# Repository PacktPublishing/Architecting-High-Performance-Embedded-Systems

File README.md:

# Architecting High-Performance Embedded Systems

This is the code repository for [Architecting High-Performance Embedded Systems](https://www.packtpub.com/product/architecting-high-performance-embedded-systems/9781789955965?utm_source=github&utm_medium=repository&utm_campaign=9781789955965), published by Packt.

**Design and build high-performance real-time digital systems based on FPGAs and custom circuits**

## What is this book about?
Modern digital devices used in homes, cars, and wearables contain highly sophisticated computing capabilities composed of embedded systems that generate, receive, and process digital data streams at rates up to multiple gigabits per second. This book will show you how to use Field Programmable Gate Arrays (FPGAs) and high-speed digital circuit design to create your own cutting-edge digital systems. 

This book covers the following exciting features:
* Understand the fundamentals of real-time embedded systems and sensors
* Discover the capabilities of FPGAs and how to use FPGA development tools
* Learn the principles of digital circuit design and PCB layout with KiCad
* Construct high-speed circuit board prototypes at low cost
* Design and develop high-performance algorithms for FPGAs
Develop robust, reliable, and efficient firmware in C
Thoroughly test and debug embedded device hardware and firmware

If you feel this book is for you, get your [copy](https://www.amazon.com/dp/1789955963) today!

## Instructions and Navigation
All of the code is organized into folders based on chapter number.

**What you need to work with the examples in this book:**
This book is for software developers, IoT engineers, and anyone who wants to understand the process of developing high-performance embedded systems. You’ll also find this book useful if you want to learn about the fundamentals of FPGA development and all aspects of firmware development in C and C++. Familiarity with the C language, digital circuits, and electronic soldering is necessary to get started.

With the following software and hardware you can run all code files present in the book.
### Software and Hardware List
| Software or hardware | OS required |
| ------------------------------------ | ----------------------------------- |
| [Xilinx Vivado](https://www.xilinx.com/support/download.html) | Windows, Mac OS X, and Linux (Any) |
| [KiCad](https://kicad.org/download/) | Windows, Mac OS X, and Linux (Any) |
| [Arty A7-100](https://www.xilinx.com/products/boards-and-kits/1-w51quh.html) | Windows, Mac OS X, and Linux (Any) |

We also provide a PDF file that has color images of the screenshots/diagrams used in this book. [Click here to download it](https://static.packt-cdn.com/downloads/9781789955965_ColorImages.pdf).

## Get to Know the Author
**Jim Ledin**
Jim Ledin is the CEO of Ledin Engineering, Inc. Jim is an expert in embedded software and hardware design, development, and testing. He is also accomplished in embedded system cybersecurity assessment and penetration testing. He has a B.S. degree in aerospace engineering from Iowa State University and an M.S. degree in electrical and computer engineering from Georgia Institute of Technology. Jim is a registered professional electrical engineer in California, a Certified Information System Security Professional (CISSP), a Certified Ethical Hacker (CEH), and a Certified Penetration Tester (CPT).

## Other books by the author
* Modern Computer Architecture and Organization [[Packt]](https://www.packtpub.com/in/cloud-networking/modern-computer-architecture-and-organization?utm_source=github&utm_medium=repository&utm_campaign=9781838984397) [[Amazon]](https://www.amazon.com/dp/1838984399)
### Download a free PDF

 <i>If you have already purchased a print or Kindle version of this book, you can get a DRM-free PDF version at no cost.<br>Simply click on the link to claim your free PDF.</i>
<p align="center"> <a href="https://packt.link/free-ebook/9781789955965">https://packt.link/free-ebook/9781789955965 </a> </p>

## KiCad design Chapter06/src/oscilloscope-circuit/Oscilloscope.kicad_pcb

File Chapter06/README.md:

__Architecting-High-Performance-Embedded-Systems__, by Jim Ledin. Published by Packt Publishing.
# Chapter 6 - Designing circuits with KiCad

This chapter introduces the excellent open source KiCad electronics design and automation suite. Working in KiCad, you design a circuit with schematic diagrams and develop a corresponding printed circuit board layout. You’ll learn how to turn a circuit board design into a prototype at a very reasonable cost. The chapter includes example schematics from the oscilloscope circuit project you will assemble in the next chapter.

After completing this chapter, you will have downloaded and installed KiCad, learned how to create circuit schematics in KiCad, learned to develop circuit board layouts in KiCad, and you will have worked through portions of the circuit board design for the digital oscilloscope project.

We will cover the following topics in this chapter: 
* Introducing KiCad
* Basic KiCad procedures
* Developing the project schematic diagram
* Laying out the PCB
* Prototyping the circuit board

# Chapter Files

[oscilloscope-circuit project](src/oscilloscope-circuit) contains the KiCad schematic diagram and PCB layout project for the digital oscilloscope circuit design we worked through in Chapter 6.

__Notes:__
* Before opening the schematic diagram, open the KiCad project manager and add *Schematic Symbols.lib* as a library using *Preferences/Manage Symbol Libraries...*
* Before opening the PCB layout, open the KiCad project manager and add the directory *Footprints.pretty* as a library using *Preferences/Manage Footprint Libraries...*

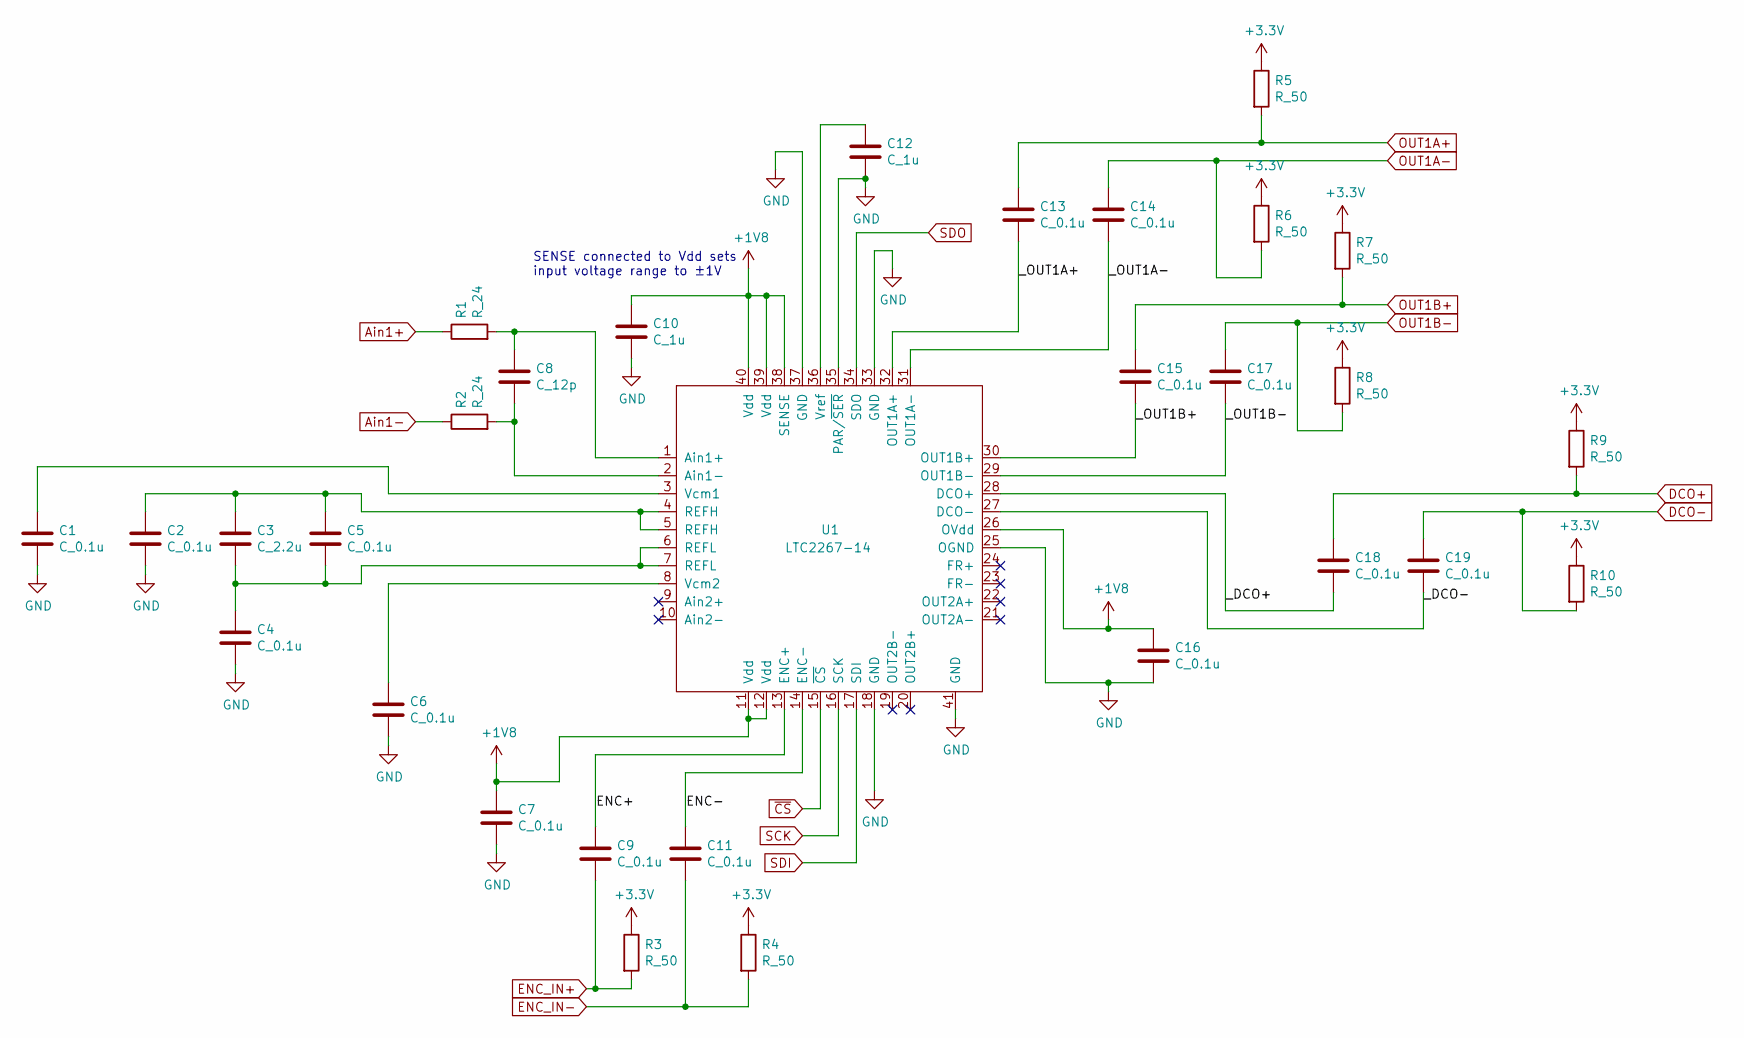
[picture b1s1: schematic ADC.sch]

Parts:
C1, C2, C4, C5, C6, C7, C9, C11, C13, C14, C15, C16, C17, C18, C19: C_0.1u; C_0402_1005Metric
C3: C_2.2u; C_0603_1608Metric
C8: C_12p; C_0402_1005Metric
C10, C12: C_1u; C_0603_1608Metric
R1, R2: R_24; R_0402_1005Metric
R3, R4, R5, R6, R7, R8, R9, R10: R_50; R_0402_1005Metric
U1: LTC2267-14; QFN-40-1EP_6x6mm_P0.5mm_EP4.6x4.6mm_ThermalVias

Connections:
+1V8: C7.1, C10.1, C16.1, U1.11 (Vdd), U1.12 (Vdd), U1.26 (OVdd), U1.38 (SENSE), U1.39 (Vdd), U1.40 (Vdd); also elsewhere on the board
+3V3: R3.1, R4.1, R5.1, R6.1, R7.1, R8.1, R9.1, R10.1; also elsewhere on the board
/ADC/ENC+: C9.1, U1.13 (ENC+)
/ADC/ENC-: C11.1, U1.14 (ENC-)
/ADC/_DCO+: C18.2, U1.28 (DCO+)
/ADC/_DCO-: C19.2, U1.27 (DCO-)
/ADC/_OUT1A+: C13.2, U1.32 (OUT1A+)
/ADC/_OUT1A-: C14.2, U1.31 (OUT1A-)
/ADC/_OUT1B+: C15.2, U1.30 (OUT1B+)
/ADC/_OUT1B-: C17.2, U1.29 (OUT1B-)
Ain1+: R1.1; also elsewhere on the board
Ain1-: R2.1; also elsewhere on the board
DCO+: C18.1, R9.2; also elsewhere on the board
DCO-: C19.1, R10.2; also elsewhere on the board
ENC_IN+: C9.2, R3.2; also elsewhere on the board
ENC_IN-: C11.2, R4.2; also elsewhere on the board
GND: C1.2, C2.2, C4.2, C6.2, C7.2, C10.2, C12.2, C16.2, U1.18 (GND), U1.25 (OGND), U1.33 (GND), U1.35 (PAR/~SER), U1.37 (GND), U1.41 (GND); also elsewhere on the board
unnamed: C1.1, U1.3 (Vcm1)
unnamed: C2.1, C3.1, C5.1, U1.4 (REFH), U1.5 (REFH)
unnamed: C3.2, C4.1, C5.2, U1.6 (REFL), U1.7 (REFL)
unnamed: C6.1, U1.8 (Vcm2)
unnamed: C8.1, R1.2, U1.1 (Ain1+)
unnamed: C8.2, R2.2, U1.2 (Ain1-)
unnamed: C12.1, U1.36 (Vref)
OUT1A+: C13.1, R5.2; also elsewhere on the board
OUT1A-: C14.1, R6.2; also elsewhere on the board
OUT1B+: C15.1, R7.2; also elsewhere on the board
OUT1B-: C17.1, R8.2; also elsewhere on the board
SCK: U1.16 (SCK); also elsewhere on the board
SDI: U1.17 (SDI); also elsewhere on the board
SDO: U1.34 (SDO); also elsewhere on the board
~CS: U1.15 (~CS); also elsewhere on the board

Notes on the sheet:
SENSE connected to Vdd sets input voltage range to ±1V

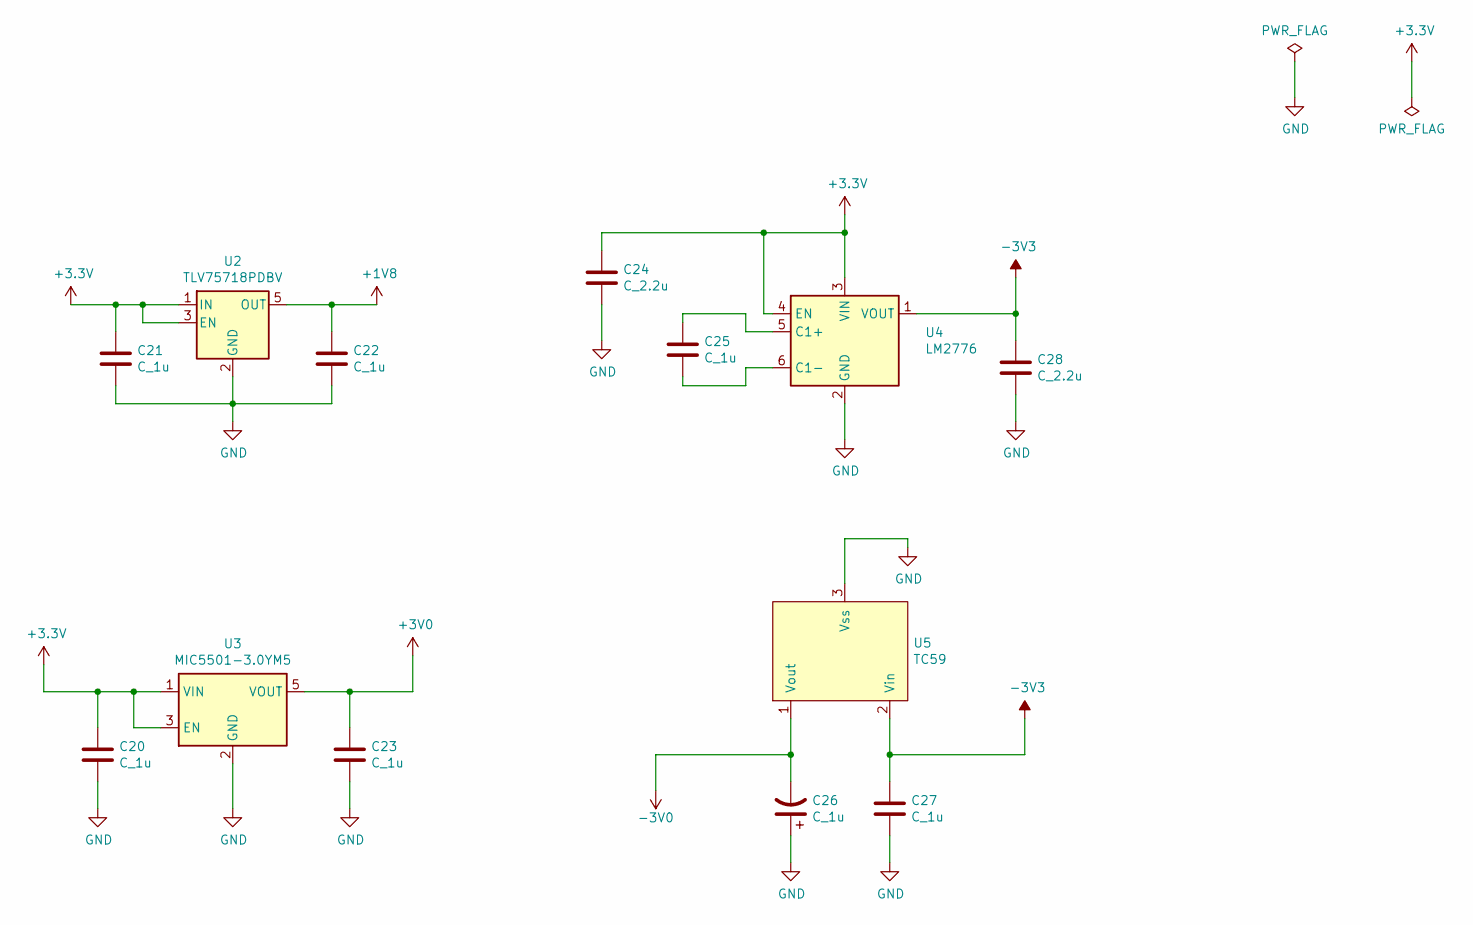
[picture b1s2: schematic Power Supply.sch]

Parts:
C20, C21, C22, C23, C25, C27: C_1u; C_0603_1608Metric
C24, C28: C_2.2u; C_0603_1608Metric
C26: C_1u; CP_EIA-2012-12_Kemet-R
U2: TLV75718PDBV; SOT-23-5
U3: MIC5501-3.0YM5; SOT-23-5
U4: LM2776; SOT-23-6
U5: TC59; SOT-23

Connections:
+1V8: C22.1, U2.5 (OUT); also elsewhere on the board
+3V0: C23.1, U3.5 (VOUT); also elsewhere on the board
+3V3: C20.1, C21.1, C24.1, U2.1 (IN), U2.3 (EN), U3.1 (VIN), U3.3 (EN), U4.3 (VIN), U4.4 (EN); also elsewhere on the board
-3V0: C26.2, U5.1 (Vout); also elsewhere on the board
-3V3: C27.1, C28.1, U4.1 (VOUT), U5.2 (Vin)
GND: C20.2, C21.2, C22.2, C23.2, C24.2, C26.1, C27.2, C28.2, U2.2 (GND), U3.2 (GND), U4.2 (GND), U5.3 (Vss); also elsewhere on the board
unnamed: C25.1, U4.5 (C1+)
unnamed: C25.2, U4.6 (C1-)

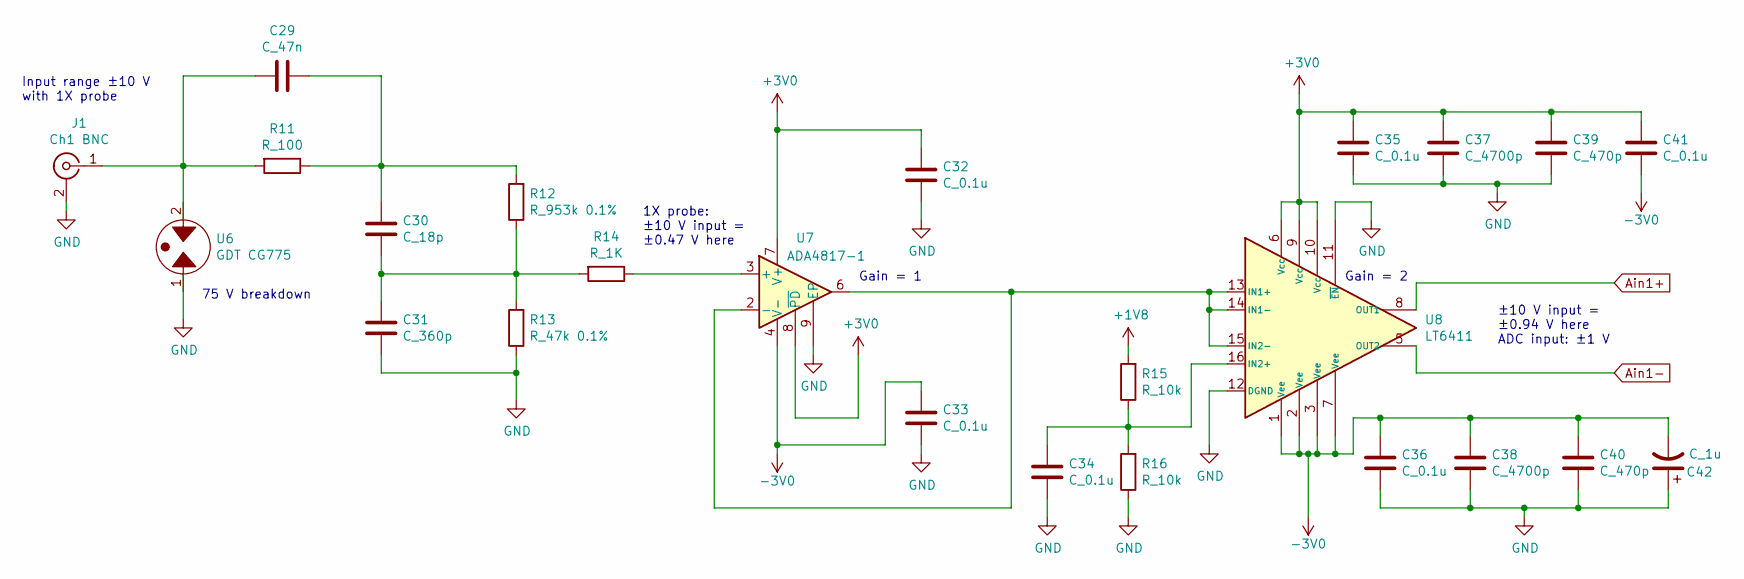
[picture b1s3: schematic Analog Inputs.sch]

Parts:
C29: C_47n; C_0402_1005Metric
C30: C_18p; C_0402_1005Metric
C31: C_360p; C_0402_1005Metric
C32, C33, C34, C35, C36, C41: C_0.1u; C_0402_1005Metric
C37, C38: C_4700p; C_0402_1005Metric
C39, C40: C_470p; C_0402_1005Metric
C42: C_1u; CP_EIA-2012-12_Kemet-R
J1: Ch1 BNC; BNC_Amphenol_B6252HB-NPP3G-50_Horizontal
R11: R_100; R_0402_1005Metric
R12: R_953k 0.1%; R_0402_1005Metric
R13: R_47k 0.1%; R_0402_1005Metric
R14: R_1K; R_0402_1005Metric
R15, R16: R_10k; R_0402_1005Metric
U6: GDT CG775; Littelfuse-GTCC23-XXXM-R01-2-Series-GDT
U7: ADA4817-1; SOIC-8-1EP_3.9x4.9mm_P1.27mm_EP2.29x3mm
U8: LT6411; QFN-16-1EP_3x3mm_P0.5mm_EP1.7x1.7mm

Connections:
+1V8: R15.2; also elsewhere on the board
+3V0: C32.2, C35.2, C37.2, C39.2, C41.2, U7.7 (V+), U7.8 (~PD), U8.6 (Vcc), U8.9 (Vcc), U8.10 (Vcc); also elsewhere on the board
-3V0: C33.2, C36.2, C38.2, C40.2, C41.1, C42.2, U7.4 (V-), U8.1 (Vee), U8.2 (Vee), U8.3 (Vee), U8.7 (Vee); also elsewhere on the board
Ain1+: U8.8 (OUT1); also elsewhere on the board
Ain1-: U8.5 (OUT2); also elsewhere on the board
GND: C31.1, C32.1, C33.1, C34.1, C35.1, C36.1, C37.1, C38.1, C39.1, C40.1, C42.1, J1.2 (Ext), R13.1, R16.1, U6.1, U7.9 (EP), U8.11 (~EN), U8.12 (DGND); also elsewhere on the board
unnamed: C29.1, C30.2, R11.1, R12.2
unnamed: C29.2, J1.1 (In), R11.2, U6.2
unnamed: C30.1, C31.2, R12.1, R13.2, R14.2
unnamed: C34.2, R15.1, R16.2, U8.16 (IN2+)
unnamed: R14.1, U7.3 (+)
unnamed: U7.2 (-), U7.6, U8.13 (IN1+), U8.14 (IN1-), U8.15 (IN2-)

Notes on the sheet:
Input range ±10 V with 1X probe
Gain = 2
1X probe: ±10 V input = ±0.47 V here
±10 V input = ±0.94 V here ADC input: ±1 V
Gain = 1
75 V breakdown

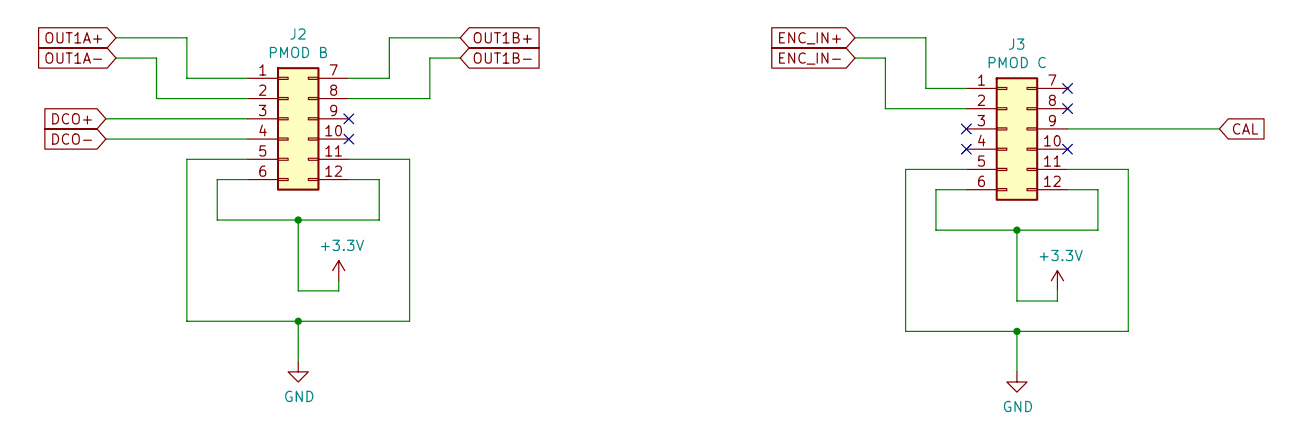
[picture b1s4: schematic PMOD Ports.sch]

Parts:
J2: PMOD B; PinHeader_2x06_P2.54mm_renumbered
J3: PMOD C; PinHeader_2x06_P2.54mm_renumbered

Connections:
+3V3: J2.6, J2.12, J3.6, J3.12; also elsewhere on the board
CAL: J3.9; also elsewhere on the board
DCO+: J2.3; also elsewhere on the board
DCO-: J2.4; also elsewhere on the board
ENC_IN+: J3.1; also elsewhere on the board
ENC_IN-: J3.2; also elsewhere on the board
GND: J2.5, J2.11, J3.5, J3.11; also elsewhere on the board
OUT1A+: J2.1; also elsewhere on the board
OUT1A-: J2.2; also elsewhere on the board
OUT1B+: J2.7; also elsewhere on the board
OUT1B-: J2.8; also elsewhere on the board

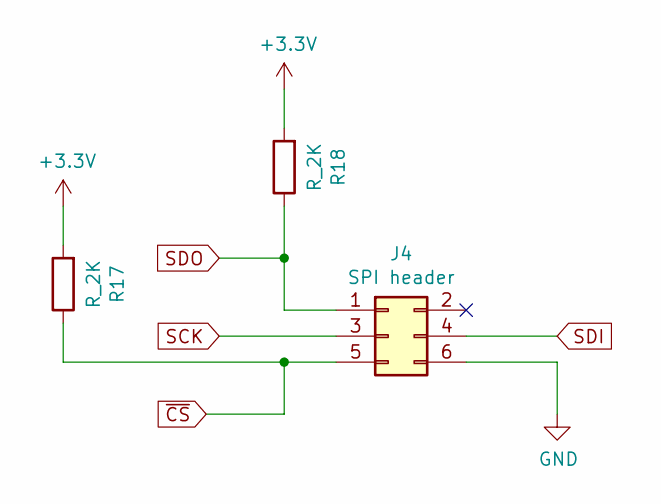
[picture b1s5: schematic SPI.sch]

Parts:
J4: SPI header; PinHeader_2x03_P2.54mm_Vertical
R17, R18: R_2K; R_0402_1005Metric

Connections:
+3V3: R17.2, R18.2; also elsewhere on the board
GND: J4.6; also elsewhere on the board
SCK: J4.3; also elsewhere on the board
SDI: J4.4; also elsewhere on the board
SDO: J4.1, R18.1; also elsewhere on the board
~CS: J4.5, R17.1; also elsewhere on the board

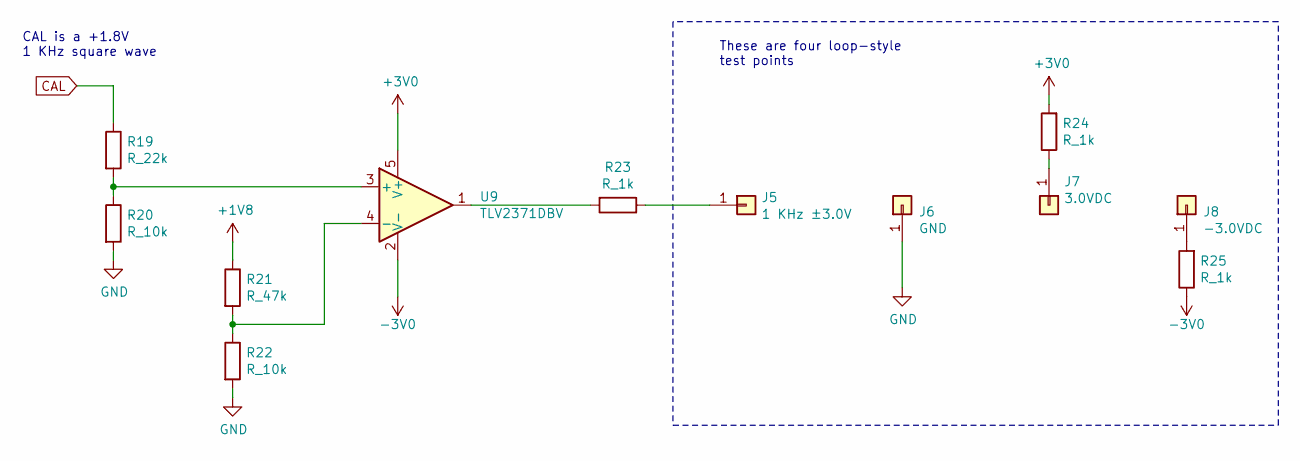
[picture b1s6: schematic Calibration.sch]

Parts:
J5: 1 KHz ±3.0V; TestPoint_Loop_D2.60mm_Drill1.6mm_Beaded
J6: GND; TestPoint_Loop_D2.60mm_Drill1.6mm_Beaded
J7: 3.0VDC; TestPoint_Loop_D2.60mm_Drill1.6mm_Beaded
J8: -3.0VDC; TestPoint_Loop_D2.60mm_Drill1.6mm_Beaded
R19: R_22k; R_0402_1005Metric
R20, R22: R_10k; R_0402_1005Metric
R21: R_47k; R_0402_1005Metric
R23, R24, R25: R_1k; R_0402_1005Metric
U9: TLV2371DBV; SOT-23-5

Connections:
+1V8: R21.1; also elsewhere on the board
+3V0: R24.2, U9.5 (V+); also elsewhere on the board
-3V0: R25.1, U9.2 (V-); also elsewhere on the board
CAL: R19.1; also elsewhere on the board
GND: J6.1, R20.2, R22.2; also elsewhere on the board
unnamed: J5.1, R23.1
unnamed: J7.1, R24.1
unnamed: J8.1, R25.2
unnamed: R19.2, R20.1, U9.3 (+)
unnamed: R21.2, R22.1, U9.4 (-)
unnamed: R23.2, U9.1

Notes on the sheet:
CAL is a +1.8V 1 KHz square wave
These are four loop-style test points

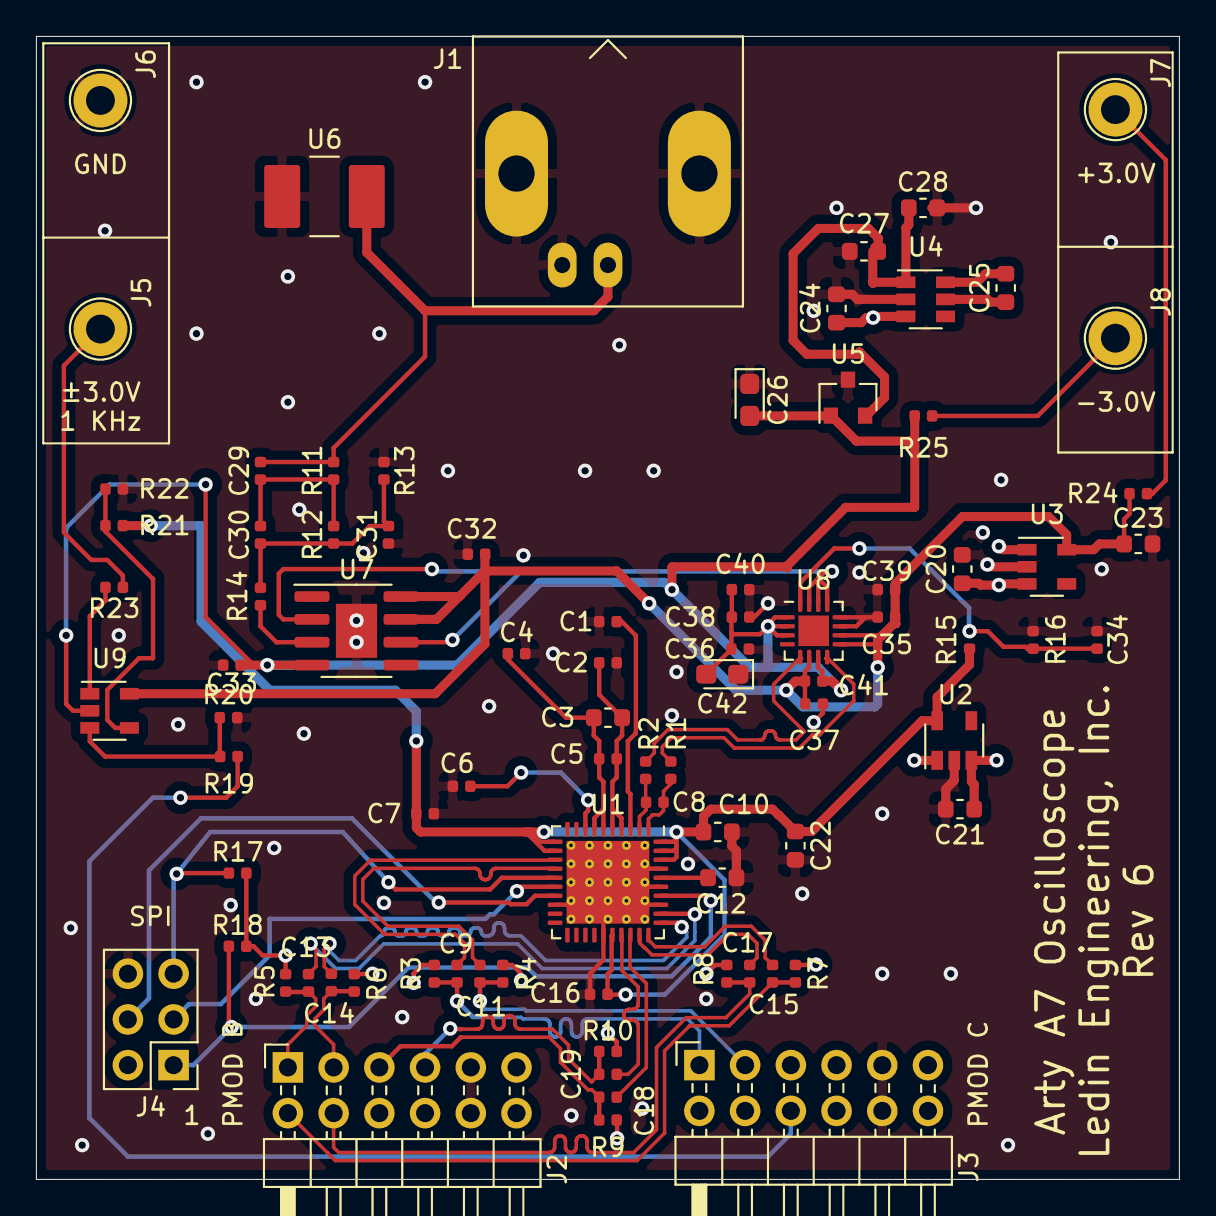
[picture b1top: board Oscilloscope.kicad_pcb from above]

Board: 4 copper layers, 63.5 x 63.5 mm, 84 parts (0 on the bottom side), 50 nets.

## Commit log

2020-10-08 Working on chapter 1
2020-10-08 Working on chapter 4
2020-10-08 Working on chapter 2
2020-10-08 Working on chapter 3
2020-10-09 Working on chapter 5
2020-10-09 Working on chapter 6
2020-10-09 Working on chapter 7
2020-10-09 Working on chapter 8
2020-10-09 Working chapters 5 and 8
2020-10-09 Working on chapters 5 and 8
2020-12-15 add $5 campaign
2021-01-16 Added chapters 9 and 10
2021-01-21 remove $5 campaign
2021-12-01 Working on Chapter 9.
2022-05-26 add $10 campaign
2022-06-14 remove $10 campaign
2022-10-24 add free ebook notification
2023-01-24 remove 5$ campaign - 2022
